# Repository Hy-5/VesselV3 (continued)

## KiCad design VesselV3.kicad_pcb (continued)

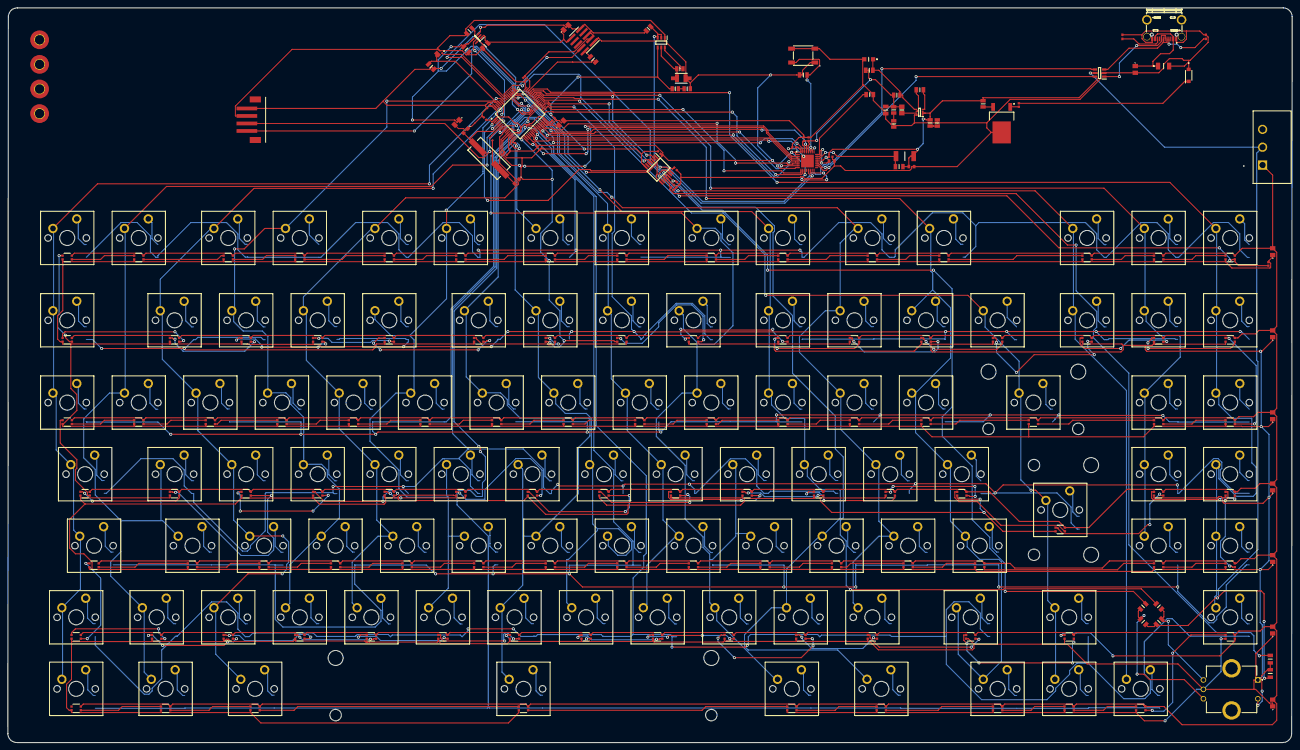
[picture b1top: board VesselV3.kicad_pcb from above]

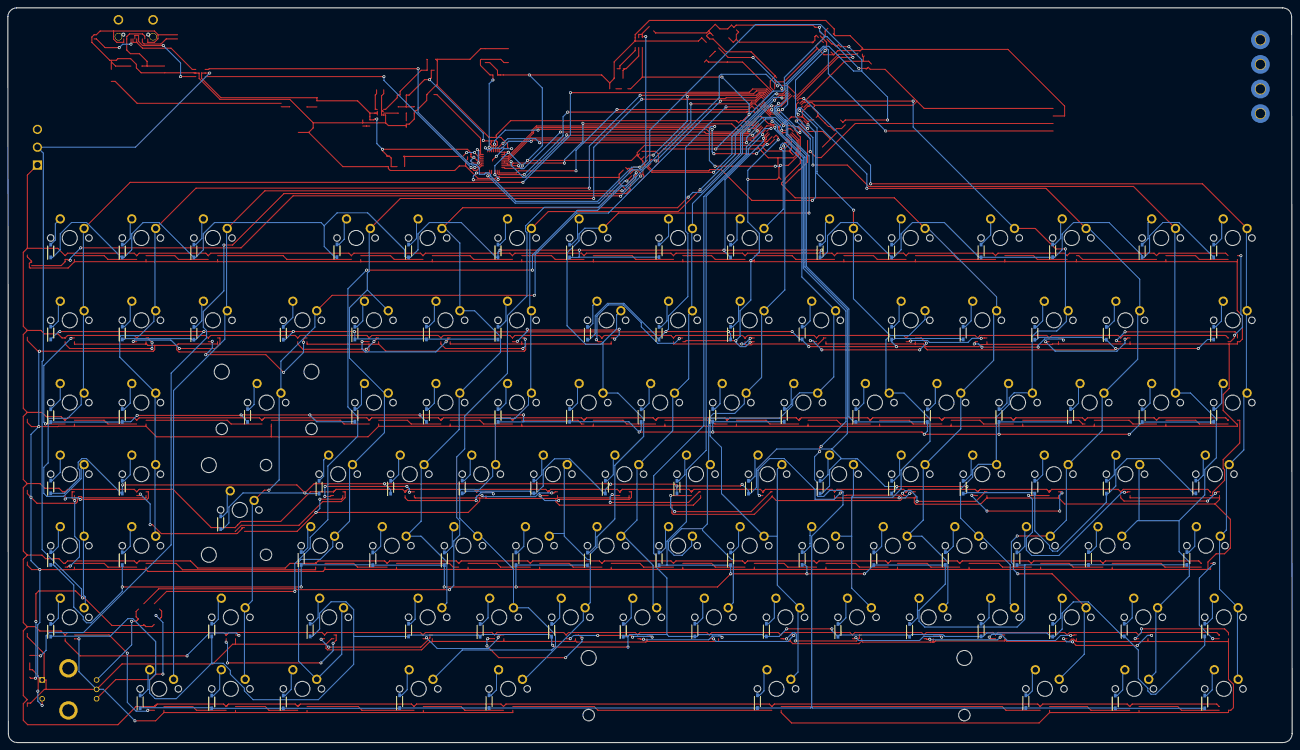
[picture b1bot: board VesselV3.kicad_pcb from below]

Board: 2 copper layers, 341.8 x 195.5 mm, 398 parts (102 on the bottom side), 292 nets.

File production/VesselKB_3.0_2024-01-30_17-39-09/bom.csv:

Designator,Footprint,Quantity,Value,LCSC Part #
(AND_Gate)IC6,SOT65P212X110-5N,1,74AUP1G09GW-Q100H,
(BidirectionalLogicLevelShifter)IC4,SOP65P640X120-14N,1,TXB0104PWR,
(LDORegulator)IC1,SOT95P282X130-5N,1,AP2112K-3.3TRG1,
(LF50ABDT-TR)-IC3,TO228P972X240-3N,1,5VOutput_VoltageRegulator,
"C1, C2",C0603,2,20pF,
"C10, C11, C12, C13, C14, C15, C18, C29, C9",C0805,9,4.7u,
"C25, C26, C27, C28, C30, C31, C32, C38, C39, C42",CAPC1005X55N,10,0.1uF,
"C3, C8",C0805,2,0.1u,
C33,CAPC2012X140N,1,10uF,
"C36, C37, C41",CAPC1005X56N,3,0.01u,
"C4, C5",CAPC2012X140N,2,1u,
"D1, D10, D100, D101, D102, D11, D12, D13, D14, D15, D16, D17, D18, D19, D2, D20, D21, D22, D23, D24, D25, D26, D27, D28, D29, D3, D30, D31, D32, D33, D34, D35, D36, D37, D38, D39, D4, D40, D41, D42, D43, D44, D45, D46, D47, D48, D49, D5, D50, D51, D52, D53, D54, D55, D56, D57, D58, D59, D6, D60, D61, D62, D63, D64, D65, D66, D67, D68, D69, D7, D70, D71, D72, D73, D74, D75, D76, D77, D78, D79, D8, D80, D81, D82, D83, D84, D85, D86, D87, D88, D89, D9, D90, D91, D92, D93, D94, D95, D96, D97, D98, D99",SODFL3816X120N,102,D_Small,
D103,SOT95P280X145-6N,1,USBLC6-2SC6Y,
"H1, H3, H4, H5",MountingHole_5.5mm,4,MountingHole,
H2,MountingHole_7mm,1,MountingHole,
J1,HUSSP10W40P127_2X5_635X340X420P,1,JTAG/SWD 10pins Headers,
JSTPH4-PIN1,4392,1,4392,
"LED1, LED10, LED100, LED101, LED102, LED11, LED12, LED13, LED14, LED15, LED16, LED17, LED18, LED19, LED2, LED20, LED21, LED22, LED23, LED24, LED25, LED26, LED27, LED28, LED29, LED3, LED30, LED31, LED32, LED33, LED34, LED35, LED36, LED37, LED38, LED39, LED4, LED40, LED41, LED42, LED43, LED44, LED45, LED46, LED47, LED48, LED49, LED5, LED50, LED51, LED52, LED53, LED54, LED55, LED56, LED57, LED58, LED59, LED6, LED60, LED61, LED62, LED63, LED64, LED65, LED66, LED67, LED68, LED69, LED7, LED70, LED71, LED72, LED73, LED74, LED75, LED76, LED77, LED78, LED79, LED8, LED80, LED81, LED82, LED83, LED84, LED85, LED86, LED87, LED88, LED89, LED9, LED90, LED91, LED92, LED93, LED94, LED95, LED96, LED97, LED98, LED99",4684_ADA,102,4684,
MCU1,QFP50P1200X1200X160-64N,1,STM32F446RET6TR,
"MX1, MX10, MX100, MX101, MX102, MX11, MX12, MX13, MX14, MX15, MX16, MX17, MX18, MX19, MX2, MX20, MX21, MX22, MX23, MX24, MX25, MX26, MX27, MX28, MX29, MX3, MX30, MX31, MX32, MX33, MX34, MX35, MX36, MX37, MX38, MX39, MX4, MX40, MX41, MX42, MX43, MX44, MX46, MX47, MX49, MX5, MX50, MX51, MX52, MX53, MX54, MX55, MX56, MX57, MX58, MX59, MX6, MX60, MX62, MX63, MX65, MX66, MX67, MX68, MX69, MX7, MX70, MX71, MX72, MX73, MX74, MX75, MX76, MX77, MX78, MX8, MX80, MX81, MX82, MX83, MX84, MX85, MX86, MX87, MX88, MX89, MX9, MX90, MX92, MX93",SW_Cherry_MX_PCB_1.00u,90,MX_SW_solder,
MX45,SW_Cherry_MX_PCB_2.00u,1,MX_SW_solder,
MX48,SW_Cherry_MX_PCB_1.50u,1,MX_SW_solder,
MX61,SW_Cherry_MX_PCB_ISOEnter,1,MX_SW_solder,
"MX64, MX91",SW_Cherry_MX_PCB_1.75u,2,MX_SW_solder,
"MX79, MX94, MX95, MX96, MX98, MX99",SW_Cherry_MX_PCB_1.25u,6,MX_SW_solder,
MX97,SW_Cherry_MX_PCB_6.25u,1,MX_SW_solder,
Polyfuse1,1206L05015YR,1,500mA,
Q1,SOT95P230X110-3N,1,"BC856A,215",
"R1, R15",RESC1005X40N,2,5.1 kOhms,
R10,RESC1005X40N,1,320,
R11,RESC2012X50N,1,22,
"R12, R13, R14, R16, R18, R19, R21, R22, R4",RESC2012X50N,9,10k,
Rotary_Encoder(20mm)_S4,PEC12R3220FS0024,1,PEC12R-3220F-S0024,
"S1, S2",Stabilizer_Cherry_MX_2.00u,2,MX_stab,
S3,Stabilizer_Cherry_MX_6.25u,1,MX_stab,
S6,SW_L102021ML04Q,1,On/On SPDT,
Schottky/ReversPolProtec1,PMEG2010ER115,1,"PMEG2010ER,115",
TVSDiode/ESDSuppr1,SODFL3618X108N,1,SMF6.0CA,
USB-C1,USB480003A,1,USB4800-03-A,
Y1,ATS25ASM1E,1,25MHz,

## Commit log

2023-11-10 Buck Converter and inductor added
2023-11-11 On/Off DPDT - Electrolytic Cap - Initial LED
2023-11-12 OLED indicator- LED arrays - minor fixes
2023-11-17 Fixed LED connection and positioning
2023-11-21 Fixing oscillator parallel connection
2023-11-21 OTG_HS_ULPI Initial Config - 1v8 Buck Added
2023-11-22 Fixed External Oscillator Circuit
2023-11-22 Final Schematics - Additional Corrections WIP
2023-11-23 Page Cleanup - Decoup CAP & Pull up Resistors
2023-11-23 ESD & Reverse Pol protections / + 5V regulator
2023-11-23 Removed stray 5V, Added additional Caps
2023-11-24 USB OTG D- & D+ fixes/Additional corrections
2023-11-25 Further fixes - Ibis models added
2023-11-26 Rotary Enc 3V3 logic needs shifting to 5V (WIP)
2023-11-26 Voltage Level Translator swapped - Rotary encoder fixed
2023-11-26 DFU compat, PNP Transistor, Pull-up resistors
2023-11-26 Fixed LED GND/HSE Oscillator symbols
2023-11-28 Initial PCB Board Setup
2023-11-28 PCB layout - Initial Commit
2023-11-28 Rough PCB Layout and GPIO Pins Swaps
2023-11-29 Swapped encoder for smaller one
2023-12-05 Fully Routed PCB
2023-12-06 Fixed DRC Errors
2023-12-06 Encoder Push - Pull-up and DRC
2023-12-06 Improved routing
2023-12-07 Thermal relief spoke fixed
2023-12-08 Traces separation - DRC Fixes
2023-12-11 USB ESD -> Internal ESD in USB3320 IC
2023-12-11 Additional Fixes
2023-12-13 Before USB_HS Impedance Matching
2023-12-13 Rerouted USB Diff Pairs for 90z impedance matching
2023-12-13 Typo Fixes
2023-12-15 Set origin
2023-12-15 Led15_DI_Cap Routing fix - 3D Case Initial Commit
2023-12-15 Fixed Switch Layer
2023-12-15 Initial Case bottom layer
2023-12-16 Imported Converted OLED PCB
2023-12-16 Prelim. PMMA Case - 3 Layers (Bottom/Switch/Top)
2023-12-16 PMMA Adjustments
2023-12-16 USB VBUS trace width fixed
2023-12-16 PMMA TopLayer Keyhole adjustments
2023-12-16 Fixed PMMA height and clearance
2023-12-16 SiderCover PMMA+ Adjustments
2023-12-17 PMMA OLED Hole Adjustment
2023-12-17 WIP (Layers Normalization/PMMA integrity adjustments)
2023-12-17 Cleanup and Further integrity adjustments
2023-12-18 Aesthetics - Lining up layers
2023-12-18 Repositioned Encoder - PMMA Layer Adjustments
2023-12-18 Size Adjustments
2023-12-20 Capacitors repositioning-PMMA Layers Alignment-Keycap Swap
2023-12-21 MountingHoles/Inserts/Screws Added
2023-12-21 Small fixes to PMMA mounting holes and inserts
2023-12-21 PMMA Insert Holes adjustments
2023-12-21 Mounting Holes and PMMA Adjustments
2023-12-23 Rerouted JLCPCB - USB Zodd
2023-12-23 Fixed mounting holes
2023-12-24 Fixed PMMA Switch Layer Mounting hole
2023-12-26 Fixed Caps on Voltage Regulators
2023-12-26 Swapped BuckConvs for Dual output voltage regs
2023-12-26 Freecad PCB updated
2023-12-27 (WIP) - Simpler PCB design and routing
2023-12-27 Added 2nd (USB_FS) PCB & PMMA Layers (Schematic, Routing & PMMA)
2023-12-28 Fixed Bottom Left Mounting hole and Adjusted PMMA
2023-12-28 3V3 traces widened (0.2->0.3mm)
2023-12-29 Edge Cuts straightened, PMMA adjusted accordingly
2023-12-29 Via to Pads Clearance improved
2023-12-30 Trace clearance fixed and some silkscreen added
2023-12-30 Minor Fixes
2023-12-31 Silkscreen modified
2024-01-01 Further routing adjustments
2024-01-01 Swapped QFN 3v3 Linear Reg for SOT25 3v3 LDO Reg
2024-01-05 PCB : +4 Solder jumpers, -RPd (NRST), Routing fix
2024-01-09 FMPI²c to I²c Swap and routing fix
2024-01-12 Swapped 0402 TVS for SOD123 - Other Routing Fixes
2024-01-12 Swapped Schottky Rectifier for lower Vf
2024-01-13 Cleanup
2024-01-17 Routing adjustments - Freecad models added
2024-01-21 PMMA layers adjustments
2024-01-21 PMMA Layers Adjusted further - Final Fillets
2024-01-21 Swapped PNP Transistor QFN for SOT123 Package- Updated PMMA
2024-01-25 Misc Modifications
2024-02-01 New LDO - 1.5 Amps compatibility test start
2024-02-01 USB PD Preliminary implementation test (Deprecated)
2024-02-02 Back to 600mA LDO regulator
2024-02-05 Final test Points added - Tracks and Vias cleanup
2024-02-05 Pre 0402 Swap
2024-02-06 Swapped 0402s for 0805s
2024-02-17 Fixed front silkscreen
2024-03-10 Initial Firmware commit
2024-03-10 WS2812B - Firmware Headache - Pre Oscilloscope probing
2024-03-11 Working WS2812B Firmware
2024-03-12 Small Firmware Optimization
2024-03-14 Fully Working firmware (LED in Bitbang mode) - PWM Work In Progress
2024-03-18 NKRO, Auto Shutdown RGB/OLED, Bitbang adjustments
2024-03-19 Debounce, IO delay, tapping term adjustments
2024-03-19 Debounce time increased
2024-03-22 Firmware debounce adjustments
2024-03-22 RGB auto shut-off
2024-03-25 Further Debouncing adjustments
2024-03-26 Working OLED Caps Indicator - Animation WIP
2024-03-26 OLED Animation initial commit
2024-03-26 Working OLED - Pre Cleanup
2024-03-26 Oled code cleanup
2024-03-26 Cleanup and readme fix
2024-03-27 OLED Toggle and Auto-Timeout fixed
2024-03-27 OLED Fixes - Readme Update
2024-03-27 Small code cleanup
2024-03-28 Further code cleanup
2024-03-28 readme update
2024-04-02 Debouncing adjustment
2024-04-07 Firmware fixes
2024-04-28 Misc Updates
2024-05-09 LED_MATRIX initial commit
2024-05-09 LED_MATRIX fixed
2024-05-09 LED_MATRIX additional fixes
2024-06-05 Firmware precleanup
2024-06-19 Additional tap dance
2024-07-16 Debounce Adjust | Win11 Compatibility Update
2024-12-22 Added missing CAD screenshots
2024-12-22 Added larger 3D turntable demo
2024-12-22 Update README.md
    Added Case pre-production screenshots
